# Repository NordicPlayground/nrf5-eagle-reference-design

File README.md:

# Nordic semiconductor eagle reference design

## Reference designs
![alt-text][dcdc_reference]

The reference designs supplied for eagle are made by following the [general pcb design guidelines][designguidenrf52] and referencing the [altium reference layout][altiumreference].
The eagle reference design is not the official reference designs, only the Altium reference designs has been tested and verified. They are available for download in Nordic's product pages.
The reference designs include eagle files as well as pdf printouts. For BOM see the altium reference designs.

* nRF51x22_qfaa
* nRF51x22_qfaa_dcdc
* nRF52832_qfaa
* nRF52832_qfaa_dcdc
* nRF52832_qfaa_nfc

## Libraries
**The libraries are not verified, only the Altium reference designs has been tested and verified.**

### Nordic_nRF
This library contains the nRF51 and nRF52 in qfn and bga packages, as well as; capacitors, inductors, and a 32MHz and 32kHz xtal. All that is needed for the core reference design. (link?)

### Nordic_misc
This library contains the rest of the components used in the sample eagle design(s) in this repository, as well as some simple antenna suggestions.

## Antenna
In the Nordic_misc library there is supplied some suggestions for antennas, please note that antenna characteristics depends greatly on the board layout. These antennas are made according to the [whitepaper][monopole] on quarter wave monopole 2.45 GHz antennas. Remember to [tune][antuning] the antenna

## NFC
An NFC listener antenna suggestion is supplied in the Nordic_misc library, this is the antenna used in the [nRF52-DK] development kit. Remember to [tune][nfctune] the antenna.

[github]: <https://github.com/NordicPlayground/nrf5-eagle-reference-design>
[designguidenrf51]: <https://devzone.nordicsemi.com/blogs/655/general-pcb-design-guidelines-for-nrf51/>
[designguidenrf52]: <https://devzone.nordicsemi.com/blogs/870/general-pcb-design-guidelines-for-nrf52/>
[referencecircuitry]: <https://infocenter.nordicsemi.com/index.jsp?topic=%2Fcom.nordic.infocenter.nrf52832.ps.v1.0%2Fref_circuitry.html&cp=1_2_0_51&anchor=concept_aqp_fd1_fq>
[altiumreference]: <http://infocenter.nordicsemi.com/index.jsp?topic=%2Fcom.nordic.infocenter.nrf52%2Fdita%2Fnrf52%2Fpdflinks%2Fref_layout.html&cp=1_5>
[nfctune]: <https://devzone.nordicsemi.com/blogs/957/nfc-tag-antenna-tuning/>
[nRF52-DK]: <http://www.nordicsemi.com/eng/Products/Bluetooth-low-energy2/nRF52-DK>
[dcdc_reference]: <nRF52832_qfaa_dcdc_reference.png>
[monopole]: <http://infocenter.nordicsemi.com/topic/com.nordic.infocenter.whitepapers/dita/whitepapers/pdflinks/nwp_008.html?cp=10_12>
[antuning]: <https://infocenter.nordicsemi.com/topic/com.nordic.infocenter.whitepapers/dita/whitepapers/pdflinks/nwp_017.html?cp=11_4>

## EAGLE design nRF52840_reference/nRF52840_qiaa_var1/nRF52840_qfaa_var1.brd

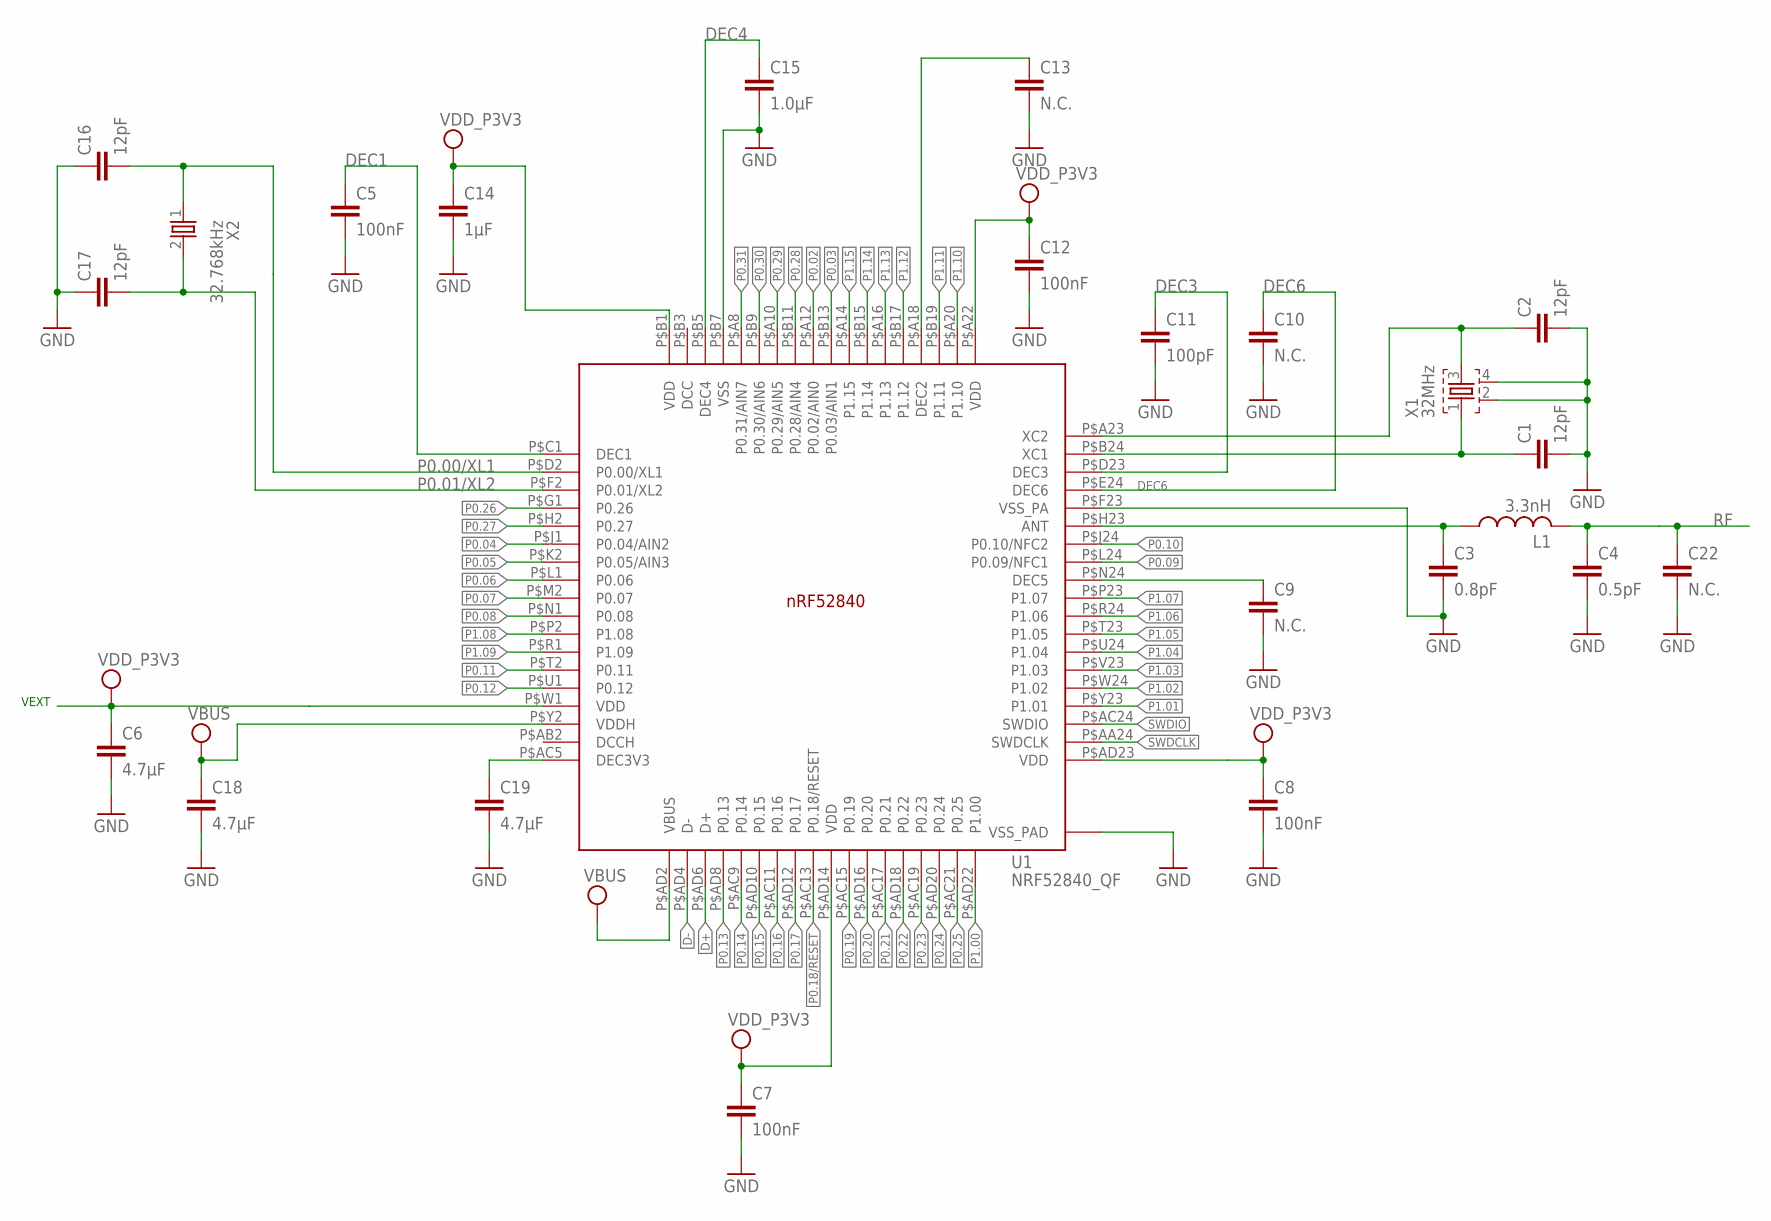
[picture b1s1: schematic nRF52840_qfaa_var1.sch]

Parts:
C1, C2, C16, C17: 12pF; RESC0402_N
C3: 0.8pF; RESC0402_N
C4: 0.5pF; RESC0402_N
C5, C7, C8, C12: 100nF; RESC0402_N
C6, C18, C19: 4.7µF; RESC0603_N
C9, C10, C13, C22: N.C.; RESC0402_N
C11: 100pF; RESC0402_N
C14: 1µF; RESC0603_N
C15: 1.0µF; RESC0603_N
L1: 3.3nH; RESC0402_N
U1: NRF52840_QF; AQFN50P700X700X85_HS-74N
X1: 32MHz; BT-XTAL_2016_N
X2: 32.768kHz; XTAL_3215_N

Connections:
ANT: C3.1, L1.1, U1.P$H23 (ANT)
D+: U1.P$AD6 (D+)
D-: U1.P$AD4 (D-)
DEC1: C5.1, U1.P$C1 (DEC1)
DEC2: C13.1, U1.P$A18 (DEC2)
DEC3: C11.1, U1.P$D23 (DEC3)
DEC3V3: C19.1, U1.P$AC5 (DEC3V3)
DEC4: C15.1, U1.P$B5 (DEC4)
DEC5: C9.1, U1.P$N24 (DEC5)
DEC6: C10.1, U1.P$E24 (DEC6)
GND: C1.2, C2.2, C3.2, C4.2, C5.2, C6.2, C7.2, C8.2, C9.2, C10.2, C11.2, C12.2, C13.2, C14.2, C15.2, C16.1, C17.1, C18.2, C19.2, C22.2, U1.P$74 (VSS_PAD), U1.P$75 (VSS_PAD), U1.P$76 (VSS_PAD), U1.P$77 (VSS_PAD), U1.P$78 (VSS_PAD), U1.P$79 (VSS_PAD), U1.P$80 (VSS_PAD), U1.P$81 (VSS_PAD), U1.P$82 (VSS_PAD), U1.P$83 (VSS_PAD), U1.P$84 (VSS_PAD), U1.P$85 (VSS_PAD), U1.P$86 (VSS_PAD), U1.P$87 (VSS_PAD), U1.P$88 (VSS_PAD), U1.P$89 (VSS_PAD), U1.P$90 (VSS_PAD), U1.P$B7 (VSS), U1.P$F23 (VSS_PA), X1.2, X1.4
P0.00/XL1: C16.2, U1.P$D2 (P0.00/XL1), X2.1
P0.01/XL2: C17.2, U1.P$F2 (P0.01/XL2), X2.2
P0.02: U1.P$A12 (P0.02/AIN0)
P0.03: U1.P$B13 (P0.03/AIN1)
P0.04: U1.P$J1 (P0.04/AIN2)
P0.05: U1.P$K2 (P0.05/AIN3)
P0.06: U1.P$L1 (P0.06)
P0.07: U1.P$M2 (P0.07)
P0.08: U1.P$N1 (P0.08)
P0.09: U1.P$L24 (P0.09/NFC1)
P0.10: U1.P$J24 (P0.10/NFC2)
P0.11: U1.P$T2 (P0.11)
P0.12: U1.P$U1 (P0.12)
P0.13: U1.P$AD8 (P0.13)
P0.14: U1.P$AC9 (P0.14)
P0.15: U1.P$AD10 (P0.15)
P0.16: U1.P$AC11 (P0.16)
P0.17: U1.P$AD12 (P0.17)
P0.18/RESET: U1.P$AC13 (P0.18/RESET)
P0.19: U1.P$AC15 (P0.19)
P0.20: U1.P$AD16 (P0.20)
P0.21: U1.P$AC17 (P0.21)
P0.22: U1.P$AD18 (P0.22)
P0.23: U1.P$AC19 (P0.23)
P0.24: U1.P$AD20 (P0.24)
P0.25: U1.P$AC21 (P0.25)
P0.26: U1.P$G1 (P0.26)
P0.27: U1.P$H2 (P0.27)
P0.28: U1.P$B11 (P0.28/AIN4)
P0.29: U1.P$A10 (P0.29/AIN5)
P0.30: U1.P$B9 (P0.30/AIN6)
P0.31: U1.P$A8 (P0.31/AIN7)
P1.00: U1.P$AD22 (P1.00)
P1.01: U1.P$Y23 (P1.01)
P1.02: U1.P$W24 (P1.02)
P1.03: U1.P$V23 (P1.03)
P1.04: U1.P$U24 (P1.04)
P1.05: U1.P$T23 (P1.05)
P1.06: U1.P$R24 (P1.06)
P1.07: U1.P$P23 (P1.07)
P1.08: U1.P$P2 (P1.08)
P1.09: U1.P$R1 (P1.09)
P1.10: U1.P$A20 (P1.10)
P1.11: U1.P$B19 (P1.11)
P1.12: U1.P$B17 (P1.12)
P1.13: U1.P$A16 (P1.13)
P1.14: U1.P$B15 (P1.14)
P1.15: U1.P$A14 (P1.15)
RF: C4.1, C22.1, L1.2
SWDCLK: U1.P$AA24 (SWDCLK)
SWDIO: U1.P$AC24 (SWDIO)
VBUS: C18.1, U1.P$AD2 (VBUS), U1.P$Y2 (VDDH)
VDD_P3V3: C6.1, C7.1, C8.1, C12.1, C14.1, U1.P$A22 (VDD), U1.P$AD14 (VDD), U1.P$AD23 (VDD), U1.P$B1 (VDD), U1.P$W1 (VDD)
XC1: C1.1, U1.P$B24 (XC1), X1.1
XC2: C2.1, U1.P$A23 (XC2), X1.3

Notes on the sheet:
VEXT

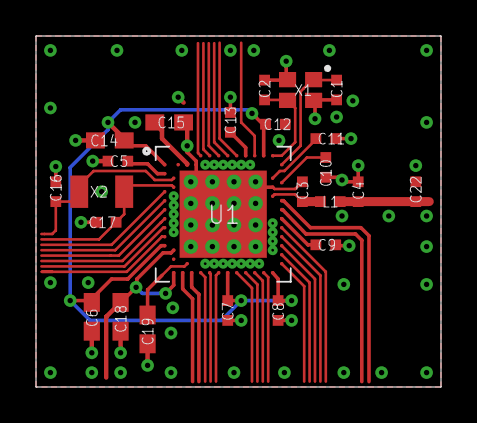
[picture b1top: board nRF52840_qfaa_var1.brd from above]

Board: 4 copper layers, 22.5 x 19.5 mm, 24 parts (0 on the bottom side), 16 nets.

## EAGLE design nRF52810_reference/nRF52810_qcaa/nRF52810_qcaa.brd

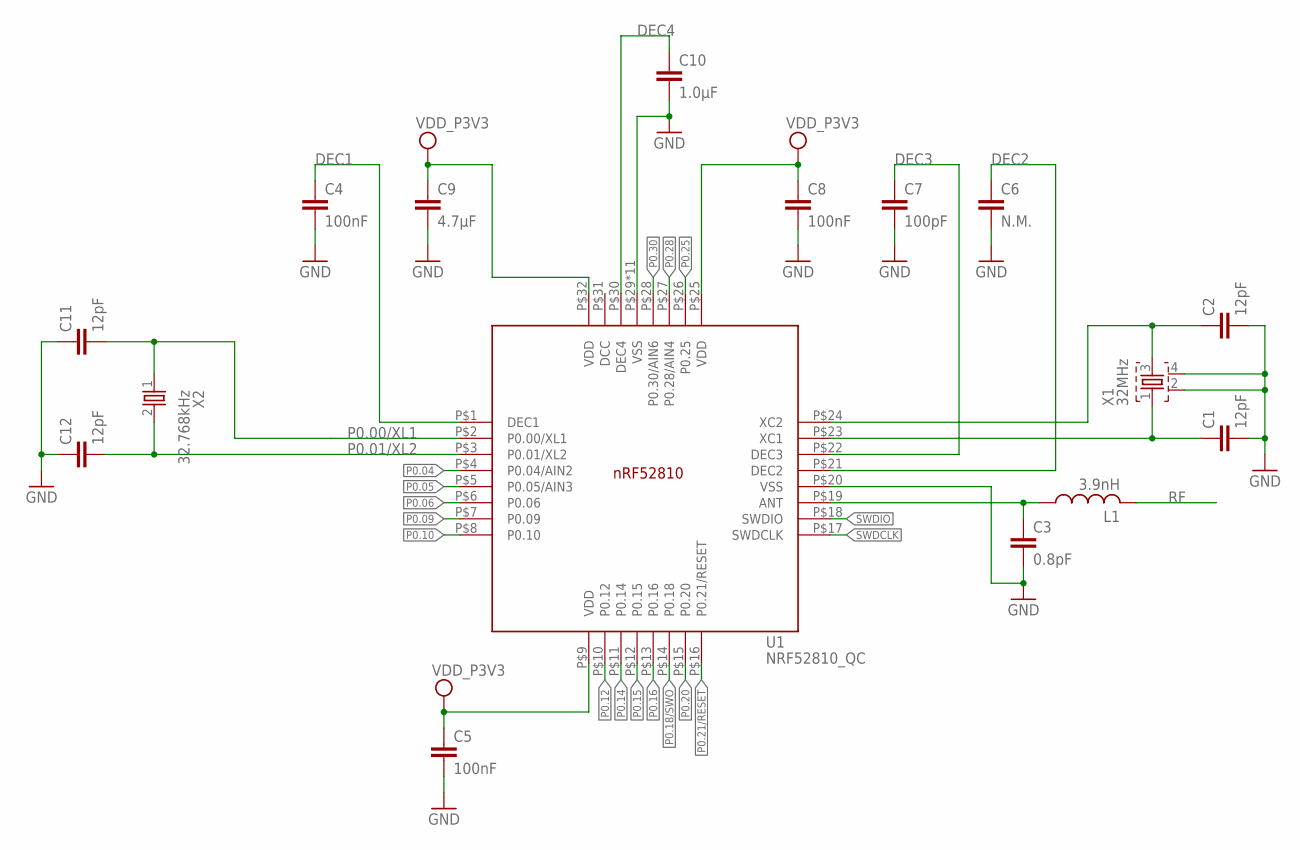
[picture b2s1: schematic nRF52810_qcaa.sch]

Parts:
C1, C2, C11, C12: 12pF; RESC0402_N
C3: 0.8pF; RESC0402_N
C4, C5, C8: 100nF; RESC0402_N
C6: N.M.; RESC0402_N
C7: 100pF; RESC0402_N
C9: 4.7µF; RESC0603_N
C10: 1.0µF; RESC0603_N
L1: 3.9nH; RESC0402_N
U1: NRF52810_QC; QFN50P500X500X90-32_N
X1: 32MHz; BT-XTAL_2016_N
X2: 32.768kHz; XTAL_3215_N

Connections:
ANT: C3.1, L1.1, U1.P$19 (ANT)
DEC1: C4.1, U1.P$1 (DEC1)
DEC2: C6.1, U1.P$21 (DEC2)
DEC3: C7.1, U1.P$22 (DEC3)
DEC4: C10.1, U1.P$30 (DEC4)
GND: C1.2, C2.2, C3.2, C4.2, C5.2, C6.2, C7.2, C8.2, C9.2, C10.2, C11.1, C12.1, U1.P$20 (VSS), U1.P$29 (VSS), U1.P$33 (VSS), U1.P$34 (VSS), U1.P$35 (VSS), U1.P$36 (VSS), U1.P$37 (VSS), U1.P$38 (VSS), U1.P$39 (VSS), U1.P$40 (VSS), U1.P$41 (VSS), U1.P$42 (VSS), X1.2, X1.4
unnamed: C2.1, U1.P$24 (XC2), X1.3
P0.00/XL1: C11.2, U1.P$2 (P0.00/XL1), X2.1
P0.01/XL2: C12.2, U1.P$3 (P0.01/XL2), X2.2
P0.04: U1.P$4 (P0.04/AIN2)
P0.05: U1.P$5 (P0.05/AIN3)
P0.06: U1.P$6 (P0.06)
P0.09: U1.P$7 (P0.09)
P0.10: U1.P$8 (P0.10)
P0.12: U1.P$10 (P0.12)
P0.14: U1.P$11 (P0.14)
P0.15: U1.P$12 (P0.15)
P0.16: U1.P$13 (P0.16)
P0.18/SWO: U1.P$14 (P0.18)
P0.20: U1.P$15 (P0.20)
P0.21/RESET: U1.P$16 (P0.21/RESET)
P0.25: U1.P$26 (P0.25)
P0.28: U1.P$27 (P0.28/AIN4)
P0.30: U1.P$28 (P0.30/AIN6)
RF: L1.2
SWDCLK: U1.P$17 (SWDCLK)
SWDIO: U1.P$18 (SWDIO)
VDD_P3V3: C5.1, C8.1, C9.1, U1.P$9 (VDD), U1.P$25 (VDD), U1.P$32 (VDD)
X1: C1.1, U1.P$23 (XC1), X1.1

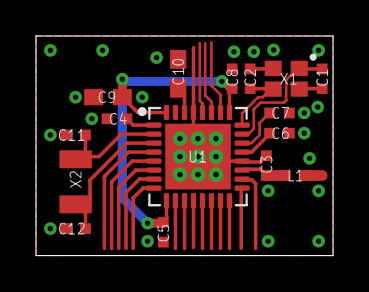
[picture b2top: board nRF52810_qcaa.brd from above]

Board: 2 copper layers, 16.5 x 12.2 mm, 16 parts (0 on the bottom side), 11 nets.

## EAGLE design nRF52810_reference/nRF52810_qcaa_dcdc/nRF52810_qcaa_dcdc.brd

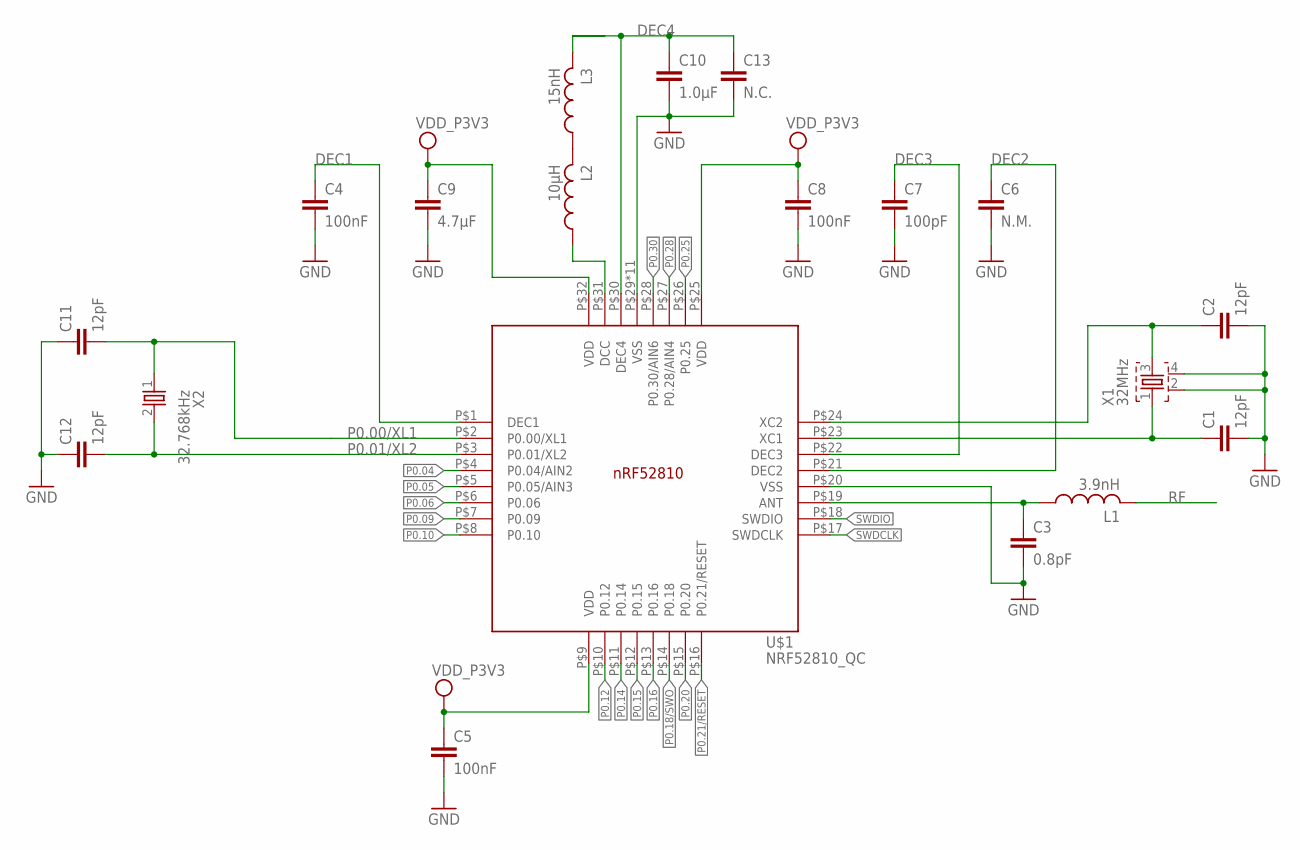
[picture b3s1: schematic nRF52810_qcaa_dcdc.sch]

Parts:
C1, C2, C11, C12: 12pF; RESC0402_N
C3: 0.8pF; RESC0402_N
C4, C5, C8: 100nF; RESC0402_N
C6: N.M.; RESC0402_N
C7: 100pF; RESC0402_N
C9: 4.7µF; RESC0603_N
C10: 1.0µF; RESC0603_N
C13: N.C.; RESC0402_N
L1: 3.9nH; RESC0402_N
L2: 10µH; RESC0603_N
L3: 15nH; RESC0402_N
U$1: NRF52810_QC; QFN50P500X500X90-32_N
X1: 32MHz; BT-XTAL_2016_N
X2: 32.768kHz; XTAL_3215_N

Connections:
ANT: C3.1, L1.1, U$1.P$19 (ANT)
DEC1: C4.1, U$1.P$1 (DEC1)
DEC2: C6.1, U$1.P$21 (DEC2)
DEC3: C7.1, U$1.P$22 (DEC3)
DEC4: C10.1, C13.1, L3.2, U$1.P$30 (DEC4)
GND: C1.2, C2.2, C3.2, C4.2, C5.2, C6.2, C7.2, C8.2, C9.2, C10.2, C11.1, C12.1, C13.2, U$1.P$20 (VSS), U$1.P$29 (VSS), U$1.P$33 (VSS), U$1.P$34 (VSS), U$1.P$35 (VSS), U$1.P$36 (VSS), U$1.P$37 (VSS), U$1.P$38 (VSS), U$1.P$39 (VSS), U$1.P$40 (VSS), U$1.P$41 (VSS), U$1.P$42 (VSS), X1.2, X1.4
unnamed: L2.2, L3.1
unnamed: C2.1, U$1.P$24 (XC2), X1.3
unnamed: L2.1, U$1.P$31 (DCC)
P0.00/XL1: C11.2, U$1.P$2 (P0.00/XL1), X2.1
P0.01/XL2: C12.2, U$1.P$3 (P0.01/XL2), X2.2
P0.04: U$1.P$4 (P0.04/AIN2)
P0.05: U$1.P$5 (P0.05/AIN3)
P0.06: U$1.P$6 (P0.06)
P0.09: U$1.P$7 (P0.09)
P0.10: U$1.P$8 (P0.10)
P0.12: U$1.P$10 (P0.12)
P0.14: U$1.P$11 (P0.14)
P0.15: U$1.P$12 (P0.15)
P0.16: U$1.P$13 (P0.16)
P0.18/SWO: U$1.P$14 (P0.18)
P0.20: U$1.P$15 (P0.20)
P0.21/RESET: U$1.P$16 (P0.21/RESET)
P0.25: U$1.P$26 (P0.25)
P0.28: U$1.P$27 (P0.28/AIN4)
P0.30: U$1.P$28 (P0.30/AIN6)
RF: L1.2
SWDCLK: U$1.P$17 (SWDCLK)
SWDIO: U$1.P$18 (SWDIO)
VDD_P3V3: C5.1, C8.1, C9.1, U$1.P$9 (VDD), U$1.P$25 (VDD), U$1.P$32 (VDD)
X1: C1.1, U$1.P$23 (XC1), X1.1

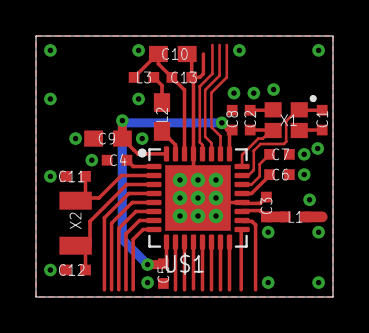
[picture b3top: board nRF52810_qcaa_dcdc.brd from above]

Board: 2 copper layers, 16.5 x 14.5 mm, 19 parts (0 on the bottom side), 13 nets.

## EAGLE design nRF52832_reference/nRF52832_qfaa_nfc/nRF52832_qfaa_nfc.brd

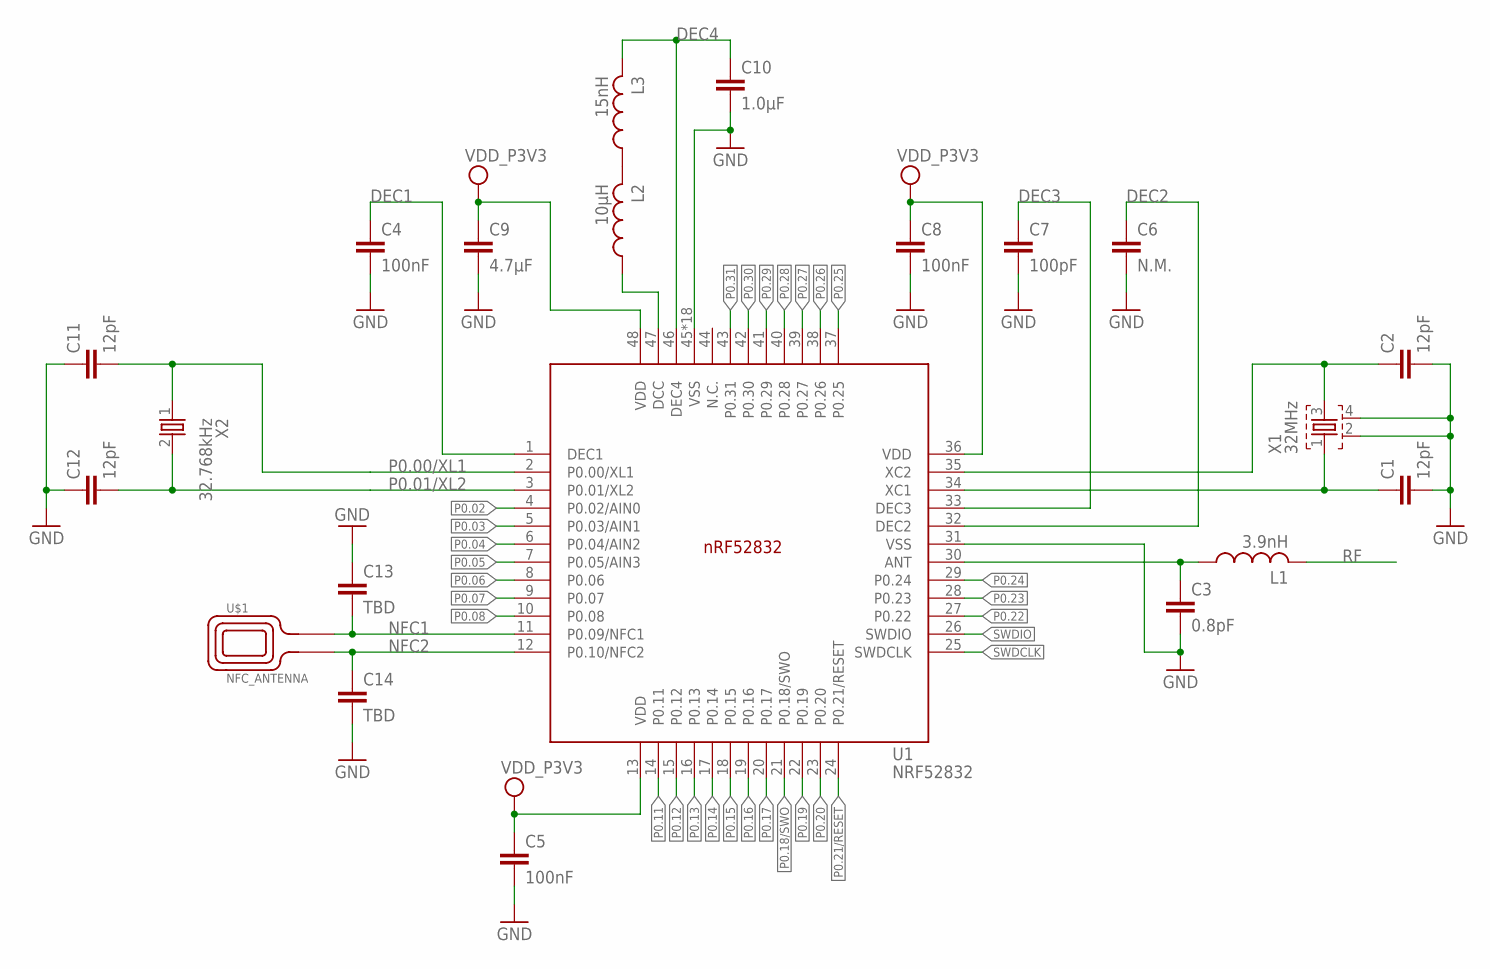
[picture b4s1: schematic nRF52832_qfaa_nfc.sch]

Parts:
C1, C2, C11, C12: 12pF; RESC0402_N
C3: 0.8pF; RESC0402_N
C4, C5, C8: 100nF; RESC0402_N
C6: N.M.; RESC0402_N
C7: 100pF; RESC0402_N
C9: 4.7µF; RESC0603_N
C10: 1.0µF; RESC0603_N
C13, C14: TBD; RESC0402_N
L1: 3.9nH; RESC0402_N
L2: 10µH; RESC0603_N
L3: 15nH; RESC0402_N
U1: NRF52832; QFN40P600X600X90-48_N
U$1: NFC_ANTENNA; NFC_ANT
X1: 32MHz; BT-XTAL_2016_N
X2: 32.768kHz; XTAL_3215_N

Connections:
ANT: C3.1, L1.1, U1.30 (ANT)
DEC1: C4.1, U1.1 (DEC1)
DEC2: C6.1, U1.32 (DEC2)
DEC3: C7.1, U1.33 (DEC3)
DEC4: C10.1, L3.2, U1.46 (DEC4)
GND: C1.2, C2.2, C3.2, C4.2, C5.2, C6.2, C7.2, C8.2, C9.2, C10.2, C11.1, C12.1, C13.1, C14.2, U1.31 (VSS), U1.45 (VSS), U1.PAD (VSS), U1.PAD@VIA01 (VSS), U1.PAD@VIA02 (VSS), U1.PAD@VIA03 (VSS), U1.PAD@VIA04 (VSS), U1.PAD@VIA05 (VSS), U1.PAD@VIA06 (VSS), U1.PAD@VIA07 (VSS), U1.PAD@VIA08 (VSS), U1.PAD@VIA09 (VSS), U1.PAD@VIA10 (VSS), U1.PAD@VIA11 (VSS), U1.PAD@VIA12 (VSS), U1.PAD@VIA13 (VSS), U1.PAD@VIA14 (VSS), U1.PAD@VIA15 (VSS), U1.PAD@VIA16 (VSS), X1.2, X1.4
unnamed: L2.2, L3.1
unnamed: C2.1, U1.35 (XC2), X1.3
unnamed: L2.1, U1.47 (DCC)
NFC1: C13.2, U1.11 (P0.09/NFC1), U$1.2
NFC2: C14.1, U1.12 (P0.10/NFC2), U$1.1
P0.00/XL1: C11.2, U1.2 (P0.00/XL1), X2.1
P0.01/XL2: C12.2, U1.3 (P0.01/XL2), X2.2
P0.02: U1.4 (P0.02/AIN0)
P0.03: U1.5 (P0.03/AIN1)
P0.04: U1.6 (P0.04/AIN2)
P0.05: U1.7 (P0.05/AIN3)
P0.06: U1.8 (P0.06)
P0.07: U1.9 (P0.07)
P0.08: U1.10 (P0.08)
P0.11: U1.14 (P0.11)
P0.12: U1.15 (P0.12)
P0.13: U1.16 (P0.13)
P0.14: U1.17 (P0.14)
P0.15: U1.18 (P0.15)
P0.16: U1.19 (P0.16)
P0.17: U1.20 (P0.17)
P0.18/SWO: U1.21 (P0.18/SWO)
P0.19: U1.22 (P0.19)
P0.20: U1.23 (P0.20)
P0.21/RESET: U1.24 (P0.21/RESET)
P0.22: U1.27 (P0.22)
P0.23: U1.28 (P0.23)
P0.24: U1.29 (P0.24)
P0.25: U1.37 (P0.25)
P0.26: U1.38 (P0.26)
P0.27: U1.39 (P0.27)
P0.28: U1.40 (P0.28)
P0.29: U1.41 (P0.29)
P0.30: U1.42 (P0.30)
P0.31: U1.43 (P0.31)
RF: L1.2
SWDCLK: U1.25 (SWDCLK)
SWDIO: U1.26 (SWDIO)
VDD_P3V3: C5.1, C8.1, C9.1, U1.13 (VDD), U1.36 (VDD), U1.48 (VDD)
X1: C1.1, U1.34 (XC1), X1.1

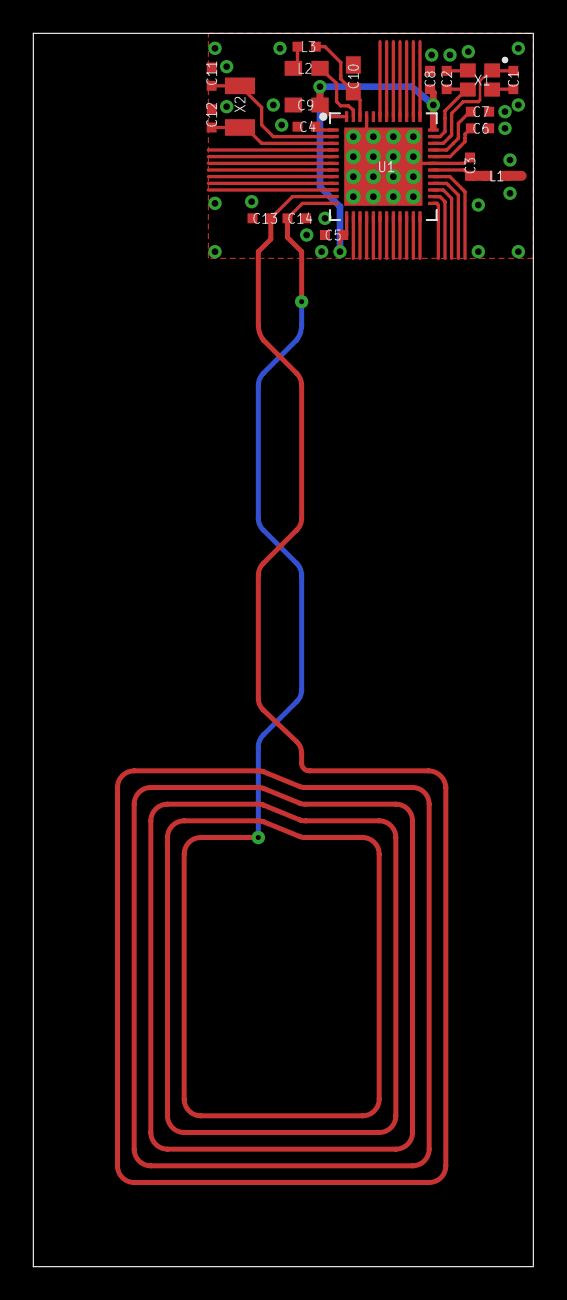
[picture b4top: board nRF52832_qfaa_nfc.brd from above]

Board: 2 copper layers, 30.0 x 74.0 mm, 21 parts (0 on the bottom side), 15 nets.

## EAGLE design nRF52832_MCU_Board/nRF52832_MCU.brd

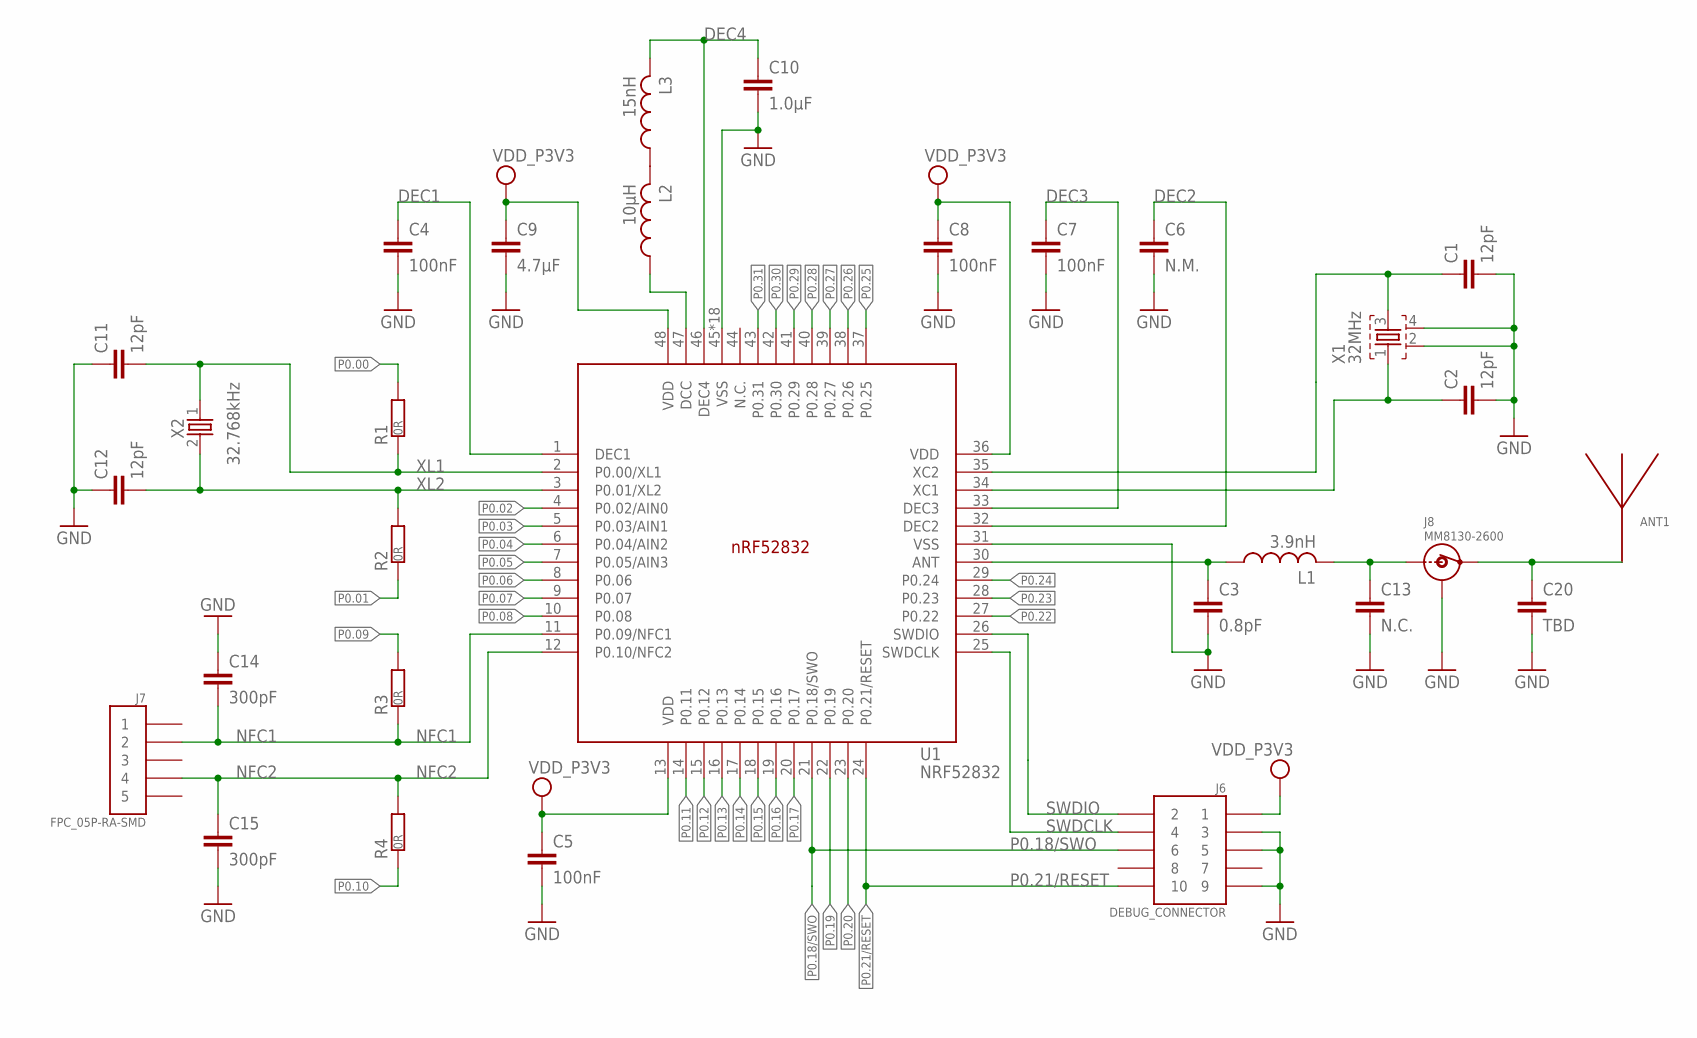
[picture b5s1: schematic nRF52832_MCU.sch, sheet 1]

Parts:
ANT1: ANTENNA_QUARTER-WAVE_MONOPOLE_MEANDERED_LEFT; QWMP_MEANDERED_LEFT_+6
C1, C2, C11, C12: 12pF; RESC0402_N
C3: 0.8pF; RESC0402_N
C4, C5, C7, C8: 100nF; RESC0402_N
C6: N.M.; RESC0402_N
C9: 4.7µF; RESC0603_N
C10: 1.0µF; RESC0603_N
C13: N.C.; RESC0402_N
C14, C15: 300pF; RESC0402_N
C20: TBD; RESC0402_N
J6: DEBUG_CONNECTOR; HDRV127P5X2-10_N
J7: FPC_05P-RA-SMD
J8: MM8130-2600
L1: 3.9nH; RESC0402_N
L2: 10µH; RESC0603_N
L3: 15nH; RESC0402_N
R1, R2, R3, R4: 0R; RESC0402_N
U1: NRF52832; QFN40P600X600X90-48_N
X1: 32MHz; BT-XTAL_2016_N
X2: 32.768kHz; XTAL_3215_N

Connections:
ANT: C3.1, L1.1, U1.30 (ANT)
DEC1: C4.1, U1.1 (DEC1)
DEC2: C6.1, U1.32 (DEC2)
DEC3: C7.1, U1.33 (DEC3)
DEC4: C10.1, L3.2, U1.46 (DEC4)
GND: C1.2, C2.2, C3.2, C4.2, C5.2, C6.2, C7.2, C8.2, C9.2, C10.2, C11.1, C12.1, C13.2, C14.1, C15.2, C20.2, J6.3, J6.5, J6.9, J8.1, J8.2, J8.3, J8.4, U1.31 (VSS), U1.45 (VSS), U1.PAD (VSS), U1.PAD@VIA01 (VSS), U1.PAD@VIA02 (VSS), U1.PAD@VIA03 (VSS), U1.PAD@VIA04 (VSS), U1.PAD@VIA05 (VSS), U1.PAD@VIA06 (VSS), U1.PAD@VIA07 (VSS), U1.PAD@VIA08 (VSS), U1.PAD@VIA09 (VSS), U1.PAD@VIA10 (VSS), U1.PAD@VIA11 (VSS), U1.PAD@VIA12 (VSS), U1.PAD@VIA13 (VSS), U1.PAD@VIA14 (VSS), U1.PAD@VIA15 (VSS), U1.PAD@VIA16 (VSS), X1.2, X1.4; also elsewhere on the board
unnamed: ANT1.P$1, C20.1, J8.OUT
unnamed: L2.2, L3.1
unnamed: C1.1, U1.35 (XC2), X1.3
unnamed: L2.1, U1.47 (DCC)
unnamed: C13.1, J8.IN, L1.2
NFC1: C14.2, J7.2, R3.1, U1.11 (P0.09/NFC1)
NFC2: C15.1, J7.4, R4.2, U1.12 (P0.10/NFC2)
P0.00: R1.2; also elsewhere on the board
P0.01: R2.1; also elsewhere on the board
P0.02: U1.4 (P0.02/AIN0); also elsewhere on the board
P0.03: U1.5 (P0.03/AIN1); also elsewhere on the board
P0.04: U1.6 (P0.04/AIN2); also elsewhere on the board
P0.05: U1.7 (P0.05/AIN3); also elsewhere on the board
P0.06: U1.8 (P0.06); also elsewhere on the board
P0.07: U1.9 (P0.07); also elsewhere on the board
P0.08: U1.10 (P0.08); also elsewhere on the board
P0.09: R3.2; also elsewhere on the board
P0.10: R4.1; also elsewhere on the board
P0.11: U1.14 (P0.11); also elsewhere on the board
P0.12: U1.15 (P0.12); also elsewhere on the board
P0.13: U1.16 (P0.13); also elsewhere on the board
P0.14: U1.17 (P0.14); also elsewhere on the board
P0.15: U1.18 (P0.15); also elsewhere on the board
P0.16: U1.19 (P0.16); also elsewhere on the board
P0.17: U1.20 (P0.17); also elsewhere on the board
P0.18/SWO: J6.6, U1.21 (P0.18/SWO); also elsewhere on the board
P0.19: U1.22 (P0.19); also elsewhere on the board
P0.20: U1.23 (P0.20); also elsewhere on the board
P0.21/RESET: J6.10, U1.24 (P0.21/RESET); also elsewhere on the board
P0.22: U1.27 (P0.22); also elsewhere on the board
P0.23: U1.28 (P0.23); also elsewhere on the board
P0.24: U1.29 (P0.24); also elsewhere on the board
P0.25: U1.37 (P0.25); also elsewhere on the board
P0.26: U1.38 (P0.26); also elsewhere on the board
P0.27: U1.39 (P0.27); also elsewhere on the board
P0.28: U1.40 (P0.28); also elsewhere on the board
P0.29: U1.41 (P0.29); also elsewhere on the board
P0.30: U1.42 (P0.30); also elsewhere on the board
P0.31: U1.43 (P0.31); also elsewhere on the board
SWDCLK: J6.4, U1.25 (SWDCLK)
SWDIO: J6.2, U1.26 (SWDIO)
VDD_P3V3: C5.1, C8.1, C9.1, J6.1, U1.13 (VDD), U1.36 (VDD), U1.48 (VDD); also elsewhere on the board
X1: C2.1, U1.34 (XC1), X1.1
XL1: C11.2, R1.1, U1.2 (P0.00/XL1), X2.1
XL2: C12.2, R2.2, U1.3 (P0.01/XL2), X2.2

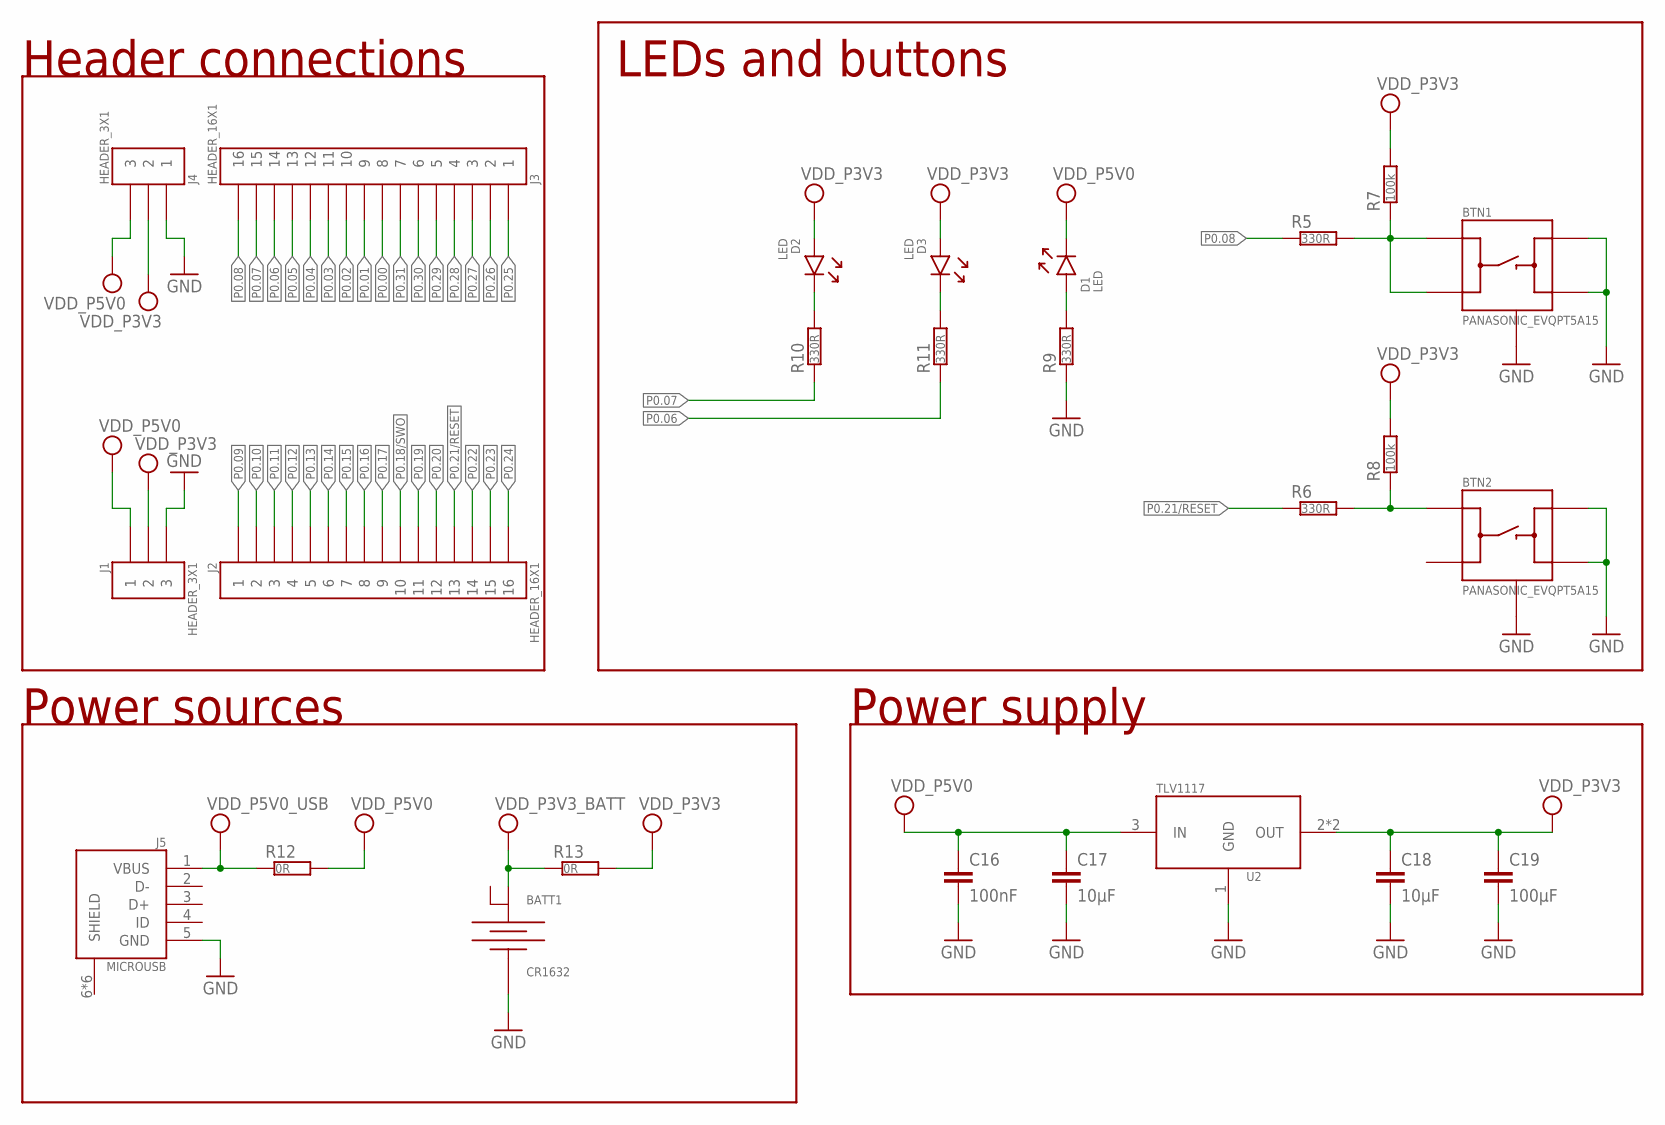
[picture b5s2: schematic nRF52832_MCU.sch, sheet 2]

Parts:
BATT1: CR1632; CR1632_HOLDER_TH
BTN1, BTN2: PANASONIC_EVQPT5A15
C16: 100nF; RESC0402_N
C17, C18: 10µF; RESC0603_N
C19: 100µF; RESC0805_N
D1, D2, D3: LED; DIOC0603_N
J1, J4: HEADER_3X1; HDRV3W64P254_1X3_762X254X900B_NO_SILK
J2, J3: HEADER_16X1; HDRV16W64P254_1X16_4064X254X900B_NO_SILK
J5: MICROUSB; USB-MICRO-B-RA-SMD-PIP
R5, R6, R9, R10, R11: 330R; RESC0402_N
R7, R8: 100k; RESC0402_N
R12, R13: 0R; RESC0402_N
U2: TLV1117; SOT220P700-4_N

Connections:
GND: BATT1.1 (-), BTN1.3 (B), BTN1.4 (B'), BTN1.5 (GND), BTN1.6 (GND), BTN2.3 (B), BTN2.4 (B'), BTN2.5 (GND), BTN2.6 (GND), C16.2, C17.2, C18.2, C19.2, J1.P$3 (3), J4.P$1 (1), J5.5 (GND), R9.1, U2.1 (GND); also elsewhere on the board
unnamed: BTN2.1 (A), R6.2, R8.1
unnamed: BTN1.1 (A), BTN1.2 (A'), R5.2, R7.1
unnamed: D2.1 (C), R10.2
unnamed: D3.1 (C), R11.2
P0.00: J3.P$8 (8); also elsewhere on the board
P0.01: J3.P$9 (9); also elsewhere on the board
P0.02: J3.P$10 (10); also elsewhere on the board
P0.03: J3.P$11 (11); also elsewhere on the board
P0.04: J3.P$12 (12); also elsewhere on the board
P0.05: J3.P$13 (13); also elsewhere on the board
P0.06: J3.P$14 (14), R11.1; also elsewhere on the board
P0.07: J3.P$15 (15), R10.1; also elsewhere on the board
P0.08: J3.P$16 (16), R5.1; also elsewhere on the board
P0.09: J2.P$1 (1); also elsewhere on the board
P0.10: J2.P$2 (2); also elsewhere on the board
P0.11: J2.P$3 (3); also elsewhere on the board
P0.12: J2.P$4 (4); also elsewhere on the board
P0.13: J2.P$5 (5); also elsewhere on the board
P0.14: J2.P$6 (6); also elsewhere on the board
P0.15: J2.P$7 (7); also elsewhere on the board
P0.16: J2.P$8 (8); also elsewhere on the board
P0.17: J2.P$9 (9); also elsewhere on the board
P0.18/SWO: J2.P$10 (10); also elsewhere on the board
P0.19: J2.P$11 (11); also elsewhere on the board
P0.20: J2.P$12 (12); also elsewhere on the board
P0.21/RESET: J2.P$13 (13), R6.1; also elsewhere on the board
P0.22: J2.P$14 (14); also elsewhere on the board
P0.23: J2.P$15 (15); also elsewhere on the board
P0.24: J2.P$16 (16); also elsewhere on the board
P0.25: J3.P$1 (1); also elsewhere on the board
P0.26: J3.P$2 (2); also elsewhere on the board
P0.27: J3.P$3 (3); also elsewhere on the board
P0.28: J3.P$4 (4); also elsewhere on the board
P0.29: J3.P$5 (5); also elsewhere on the board
P0.30: J3.P$6 (6); also elsewhere on the board
P0.31: J3.P$7 (7); also elsewhere on the board
VCC_P5V0_USB: J5.1 (VBUS), R12.1
VDD_LED: D1.2 (A), R9.2
VDD_P3V3: C18.1, C19.1, D2.2 (A), D3.2 (A), J1.P$2 (2), J4.P$2 (2), R7.2, R8.2, R13.2, U2.2 (OUT), U2.4 (OUT); also elsewhere on the board
VDD_P3V3_BATT: BATT1.2 (+), R13.1
VDD_P5V0: C16.1, C17.1, D1.1 (C), J1.P$1 (1), J4.P$3 (3), R12.2, U2.3 (IN)

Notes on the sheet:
Power supply
Power sources
Header connections
LEDs and buttons

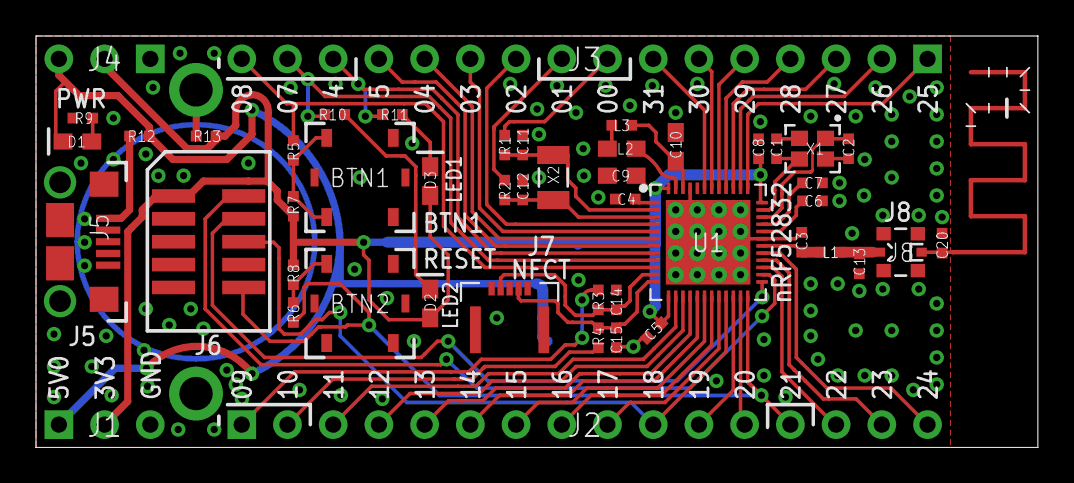
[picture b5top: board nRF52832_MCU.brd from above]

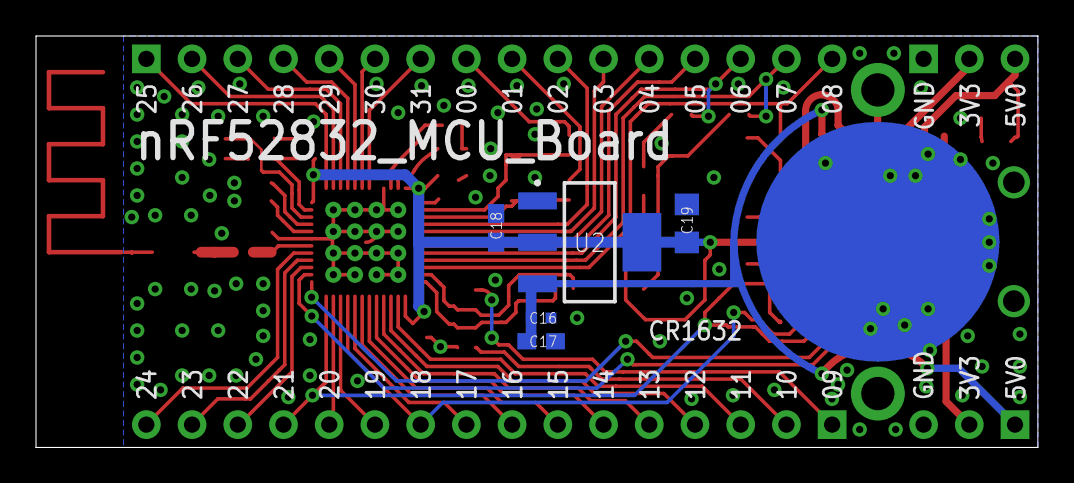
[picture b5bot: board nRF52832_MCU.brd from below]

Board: 2 copper layers, 55.7 x 22.9 mm, 55 parts (6 on the bottom side), 59 nets.
